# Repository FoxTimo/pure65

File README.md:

MCU: SuperMini NRF52840 (nice!nano clone)

LAYOUT:

SCHEMATIC:

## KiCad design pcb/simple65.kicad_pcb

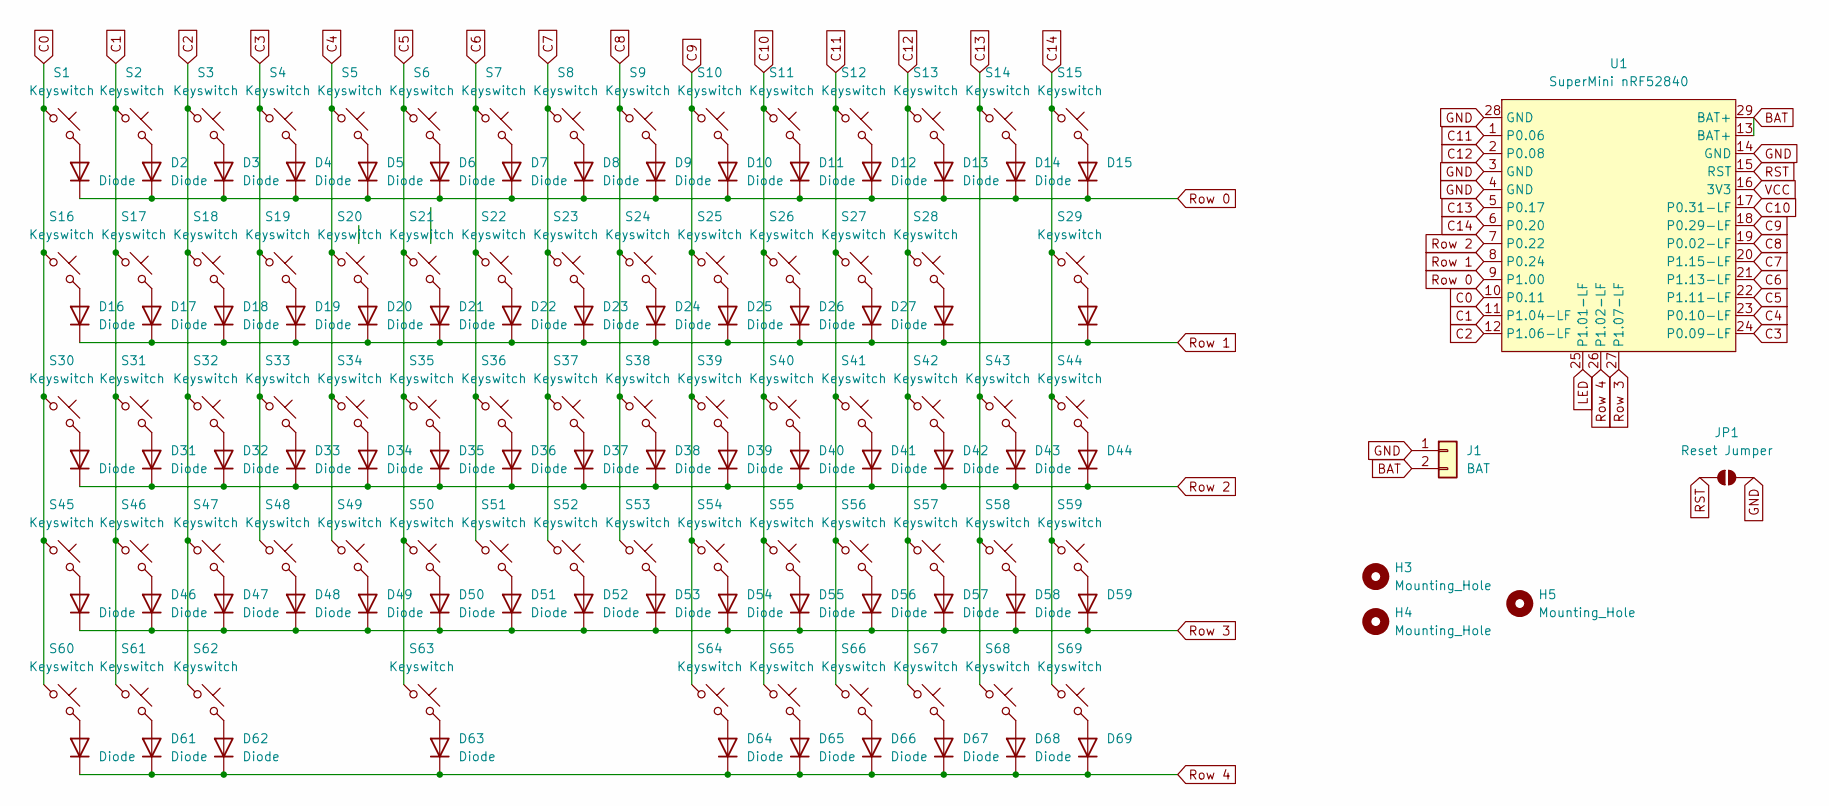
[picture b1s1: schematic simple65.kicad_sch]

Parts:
D1, D2, D3, D4, D5, D6, D7, D8, D9, D10, D11, D12, D13, D14, D15, D16, D17, D18, D19, D20, D21, D22, D23, D24, D25, D26, D27, D28, D29, D30, D31, D32, D33, D34, D35, D36, D37, D38, D39, D40, D41, D42, D43, D44, D45, D46, D47, D48, D49, D50, D51, D52, D53, D54, D55, D56, D57, D58, D59, D60, D61, D62, D63, D64, D65, D66, D67, D68, D69: Diode; Diode_DO-35
H3, H4, H5: Mounting_Hole; Mounting_Hole Pad
J1: BAT; JST_PH_S2B-PH-K_1x02_P2.00mm_Horizontal
JP1: Reset Jumper; SolderJumper-2_P1.3mm_Open_RoundedPad1.0x1.5mm
S1, S2, S3, S4, S5, S6, S7, S8, S9, S10, S11, S12, S13, S15, S17, S18, S19, S20, S21, S22, S23, S24, S25, S26, S27, S28, S29, S31, S32, S33, S34, S35, S36, S37, S38, S39, S40, S41, S42, S44, S46, S47, S48, S49, S50, S51, S52, S53, S54, S55, S56, S58, S59, S64, S65, S66, S67, S68, S69: Keyswitch; MX_PCB_1.00u
S14: Keyswitch; MX_PCB_2.00u
S16: Keyswitch; MX_PCB_1.50u
S30, S57: Keyswitch; MX_PCB_1.75u
S43: Keyswitch; MX_PCB_ISOEnter
S45, S60, S61, S62: Keyswitch; MX_PCB_1.25u
S63: Keyswitch; MX_PCB_6.25u
U1: SuperMini nRF52840; SuperMini_nRF52840_AH_Reversible

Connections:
BAT: J1.2, U1.13 (BAT+), U1.29 (BAT+)
C0: S1.1, S16.1, S30.1, S45.1, S60.1, U1.10 (P0.11)
C1: S2.1, S17.1, S31.1, S46.1, S61.1, U1.11 (P1.04-LF)
C2: S3.1, S18.1, S32.1, S47.1, S62.1, U1.12 (P1.06-LF)
C3: S4.1, S19.1, S33.1, S48.1, U1.24 (P0.09-LF)
C4: S5.1, S20.1, S34.1, S49.1, U1.23 (P0.10-LF)
C5: S6.1, S21.1, S35.1, S50.1, S63.1, U1.22 (P1.11-LF)
C6: S7.1, S22.1, S36.1, S51.1, U1.21 (P1.13-LF)
C7: S8.1, S23.1, S37.1, S52.1, U1.20 (P1.15-LF)
C8: S9.1, S24.1, S38.1, S53.1, U1.19 (P0.02-LF)
C9: S10.1, S25.1, S39.1, S54.1, S64.1, U1.18 (P0.29-LF)
C10: S11.1, S26.1, S40.1, S55.1, S65.1, U1.17 (P0.31-LF)
C11: S12.1, S27.1, S41.1, S56.1, S66.1, U1.1 (P0.06)
C12: S13.1, S28.1, S42.1, S57.1, S67.1, U1.2 (P0.08)
C13: S14.1, S43.1, S58.1, S68.1, U1.5 (P0.17)
C14: S15.1, S29.1, S44.1, S59.1, S69.1, U1.6 (P0.20)
GND: J1.1, JP1.2 (B), U1.3 (GND), U1.4 (GND), U1.14 (GND), U1.28 (GND); also elsewhere on the board
LED: U1.25 (P1.01-LF)
unnamed: D1.2 (A), S1.2
unnamed: D2.2 (A), S2.2
unnamed: D3.2 (A), S3.2
unnamed: D4.2 (A), S4.2
unnamed: D5.2 (A), S5.2
unnamed: D6.2 (A), S6.2
unnamed: D7.2 (A), S7.2
unnamed: D8.2 (A), S8.2
unnamed: D9.2 (A), S9.2
unnamed: D10.2 (A), S10.2
unnamed: D11.2 (A), S11.2
unnamed: D12.2 (A), S12.2
unnamed: D13.2 (A), S13.2
unnamed: D14.2 (A), S14.2
unnamed: D15.2 (A), S15.2
unnamed: D16.2 (A), S16.2
unnamed: D17.2 (A), S17.2
unnamed: D18.2 (A), S18.2
unnamed: D19.2 (A), S19.2
unnamed: D20.2 (A), S20.2
unnamed: D21.2 (A), S21.2
unnamed: D22.2 (A), S22.2
unnamed: D23.2 (A), S23.2
unnamed: D24.2 (A), S24.2
unnamed: D25.2 (A), S25.2
unnamed: D26.2 (A), S26.2
unnamed: D27.2 (A), S27.2
unnamed: D28.2 (A), S28.2
unnamed: D29.2 (A), S29.2
unnamed: D30.2 (A), S30.2
unnamed: D31.2 (A), S31.2
unnamed: D32.2 (A), S32.2
unnamed: D33.2 (A), S33.2
unnamed: D34.2 (A), S34.2
unnamed: D35.2 (A), S35.2
unnamed: D36.2 (A), S36.2
unnamed: D37.2 (A), S37.2
unnamed: D38.2 (A), S38.2
unnamed: D39.2 (A), S39.2
unnamed: D40.2 (A), S40.2
unnamed: D41.2 (A), S41.2
unnamed: D42.2 (A), S42.2
unnamed: D43.2 (A), S43.2
unnamed: D44.2 (A), S44.2
unnamed: D45.2 (A), S45.2
unnamed: D46.2 (A), S46.2
unnamed: D47.2 (A), S47.2
unnamed: D48.2 (A), S48.2
unnamed: D49.2 (A), S49.2
unnamed: D50.2 (A), S50.2
unnamed: D51.2 (A), S51.2
unnamed: D52.2 (A), S52.2
unnamed: D53.2 (A), S53.2
unnamed: D54.2 (A), S54.2
unnamed: D55.2 (A), S55.2
unnamed: D56.2 (A), S56.2
unnamed: D57.2 (A), S57.2
unnamed: D58.2 (A), S58.2
unnamed: D59.2 (A), S59.2
unnamed: D60.2 (A), S60.2
unnamed: D61.2 (A), S61.2
unnamed: D62.2 (A), S62.2
unnamed: D63.2 (A), S63.2
unnamed: D64.2 (A), S64.2
unnamed: D65.2 (A), S65.2
unnamed: D66.2 (A), S66.2
unnamed: D67.2 (A), S67.2
unnamed: D68.2 (A), S68.2
unnamed: D69.2 (A), S69.2
RST: JP1.1 (A), U1.15 (RST); also elsewhere on the board
Row 0: D1.1 (K), D2.1 (K), D3.1 (K), D4.1 (K), D5.1 (K), D6.1 (K), D7.1 (K), D8.1 (K), D9.1 (K), D10.1 (K), D11.1 (K), D12.1 (K), D13.1 (K), D14.1 (K), D15.1 (K), U1.9 (P1.00)
Row 1: D16.1 (K), D17.1 (K), D18.1 (K), D19.1 (K), D20.1 (K), D21.1 (K), D22.1 (K), D23.1 (K), D24.1 (K), D25.1 (K), D26.1 (K), D27.1 (K), D28.1 (K), D29.1 (K), U1.8 (P0.24)
Row 2: D30.1 (K), D31.1 (K), D32.1 (K), D33.1 (K), D34.1 (K), D35.1 (K), D36.1 (K), D37.1 (K), D38.1 (K), D39.1 (K), D40.1 (K), D41.1 (K), D42.1 (K), D43.1 (K), D44.1 (K), U1.7 (P0.22)
Row 3: D45.1 (K), D46.1 (K), D47.1 (K), D48.1 (K), D49.1 (K), D50.1 (K), D51.1 (K), D52.1 (K), D53.1 (K), D54.1 (K), D55.1 (K), D56.1 (K), D57.1 (K), D58.1 (K), D59.1 (K), U1.27 (P1.07-LF)
Row 4: D60.1 (K), D61.1 (K), D62.1 (K), D63.1 (K), D64.1 (K), D65.1 (K), D66.1 (K), D67.1 (K), D68.1 (K), D69.1 (K), U1.26 (P1.02-LF)
VCC: U1.16 (3V3)

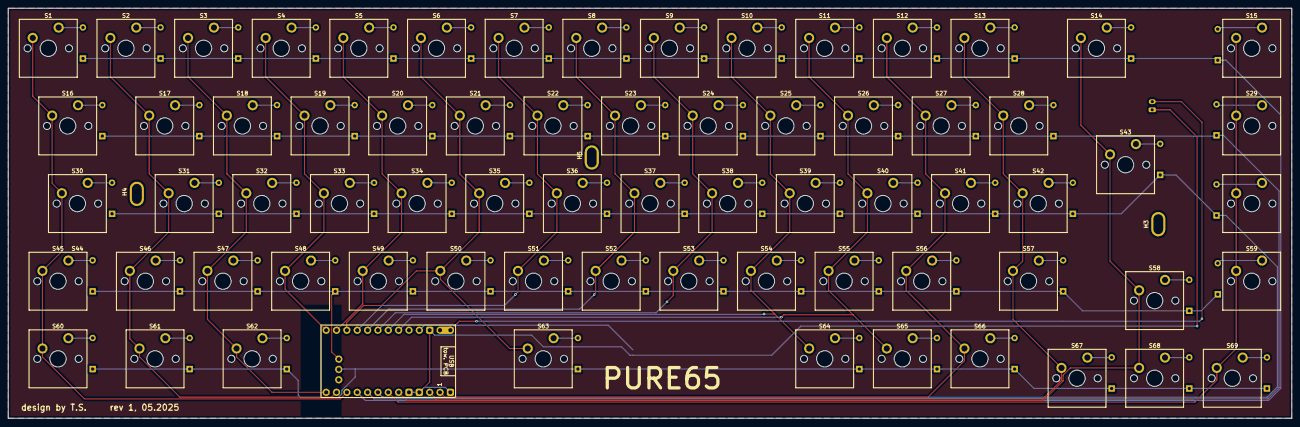
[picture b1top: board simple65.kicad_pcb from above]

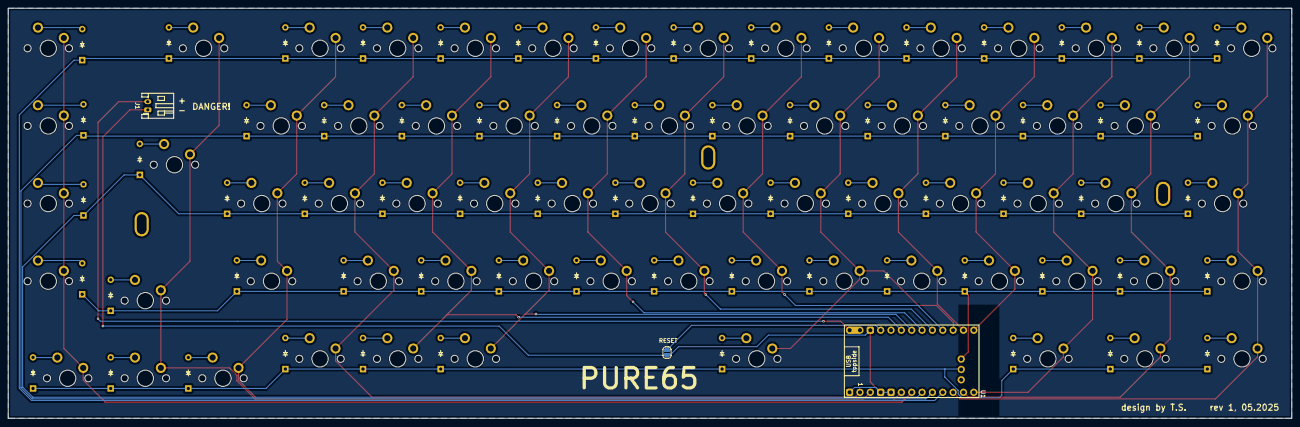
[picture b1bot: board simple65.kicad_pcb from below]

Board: 2 copper layers, 314.9 x 100.6 mm, 144 parts (72 on the bottom side), 92 nets.

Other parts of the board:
RESET: SolderJumper_2_Open; SolderJumper-2_P1.3mm_Open_RoundedPad1.0x1.5mm

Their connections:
GND: RESET.2 (B); also elsewhere on the board
RST: RESET.1 (A); also elsewhere on the board

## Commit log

2025-05-10 first setup
2025-05-10 fix bottom row
2025-05-10 implement dongle
2025-05-10 add kiCad files
